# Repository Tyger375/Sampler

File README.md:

# Sampler

**Abstract**\
The project consists of engineering an electronic musical sampler from scratch. The work combines hardware development with the implementation of dedicated software, creating a machine equipped with pressure-sensitive pads for managing audio samples, inspired by the history of hip-hop music. This experience, balancing hobby and education, has provided solid technical skills and is conceived to be constantly updated and perfected.

Read the paper [here](https://github.com/Tyger375/Sampler/blob/main/docs/out/out.pdf) \
*made with [btex](https://github.com/Tyger375/btex)*

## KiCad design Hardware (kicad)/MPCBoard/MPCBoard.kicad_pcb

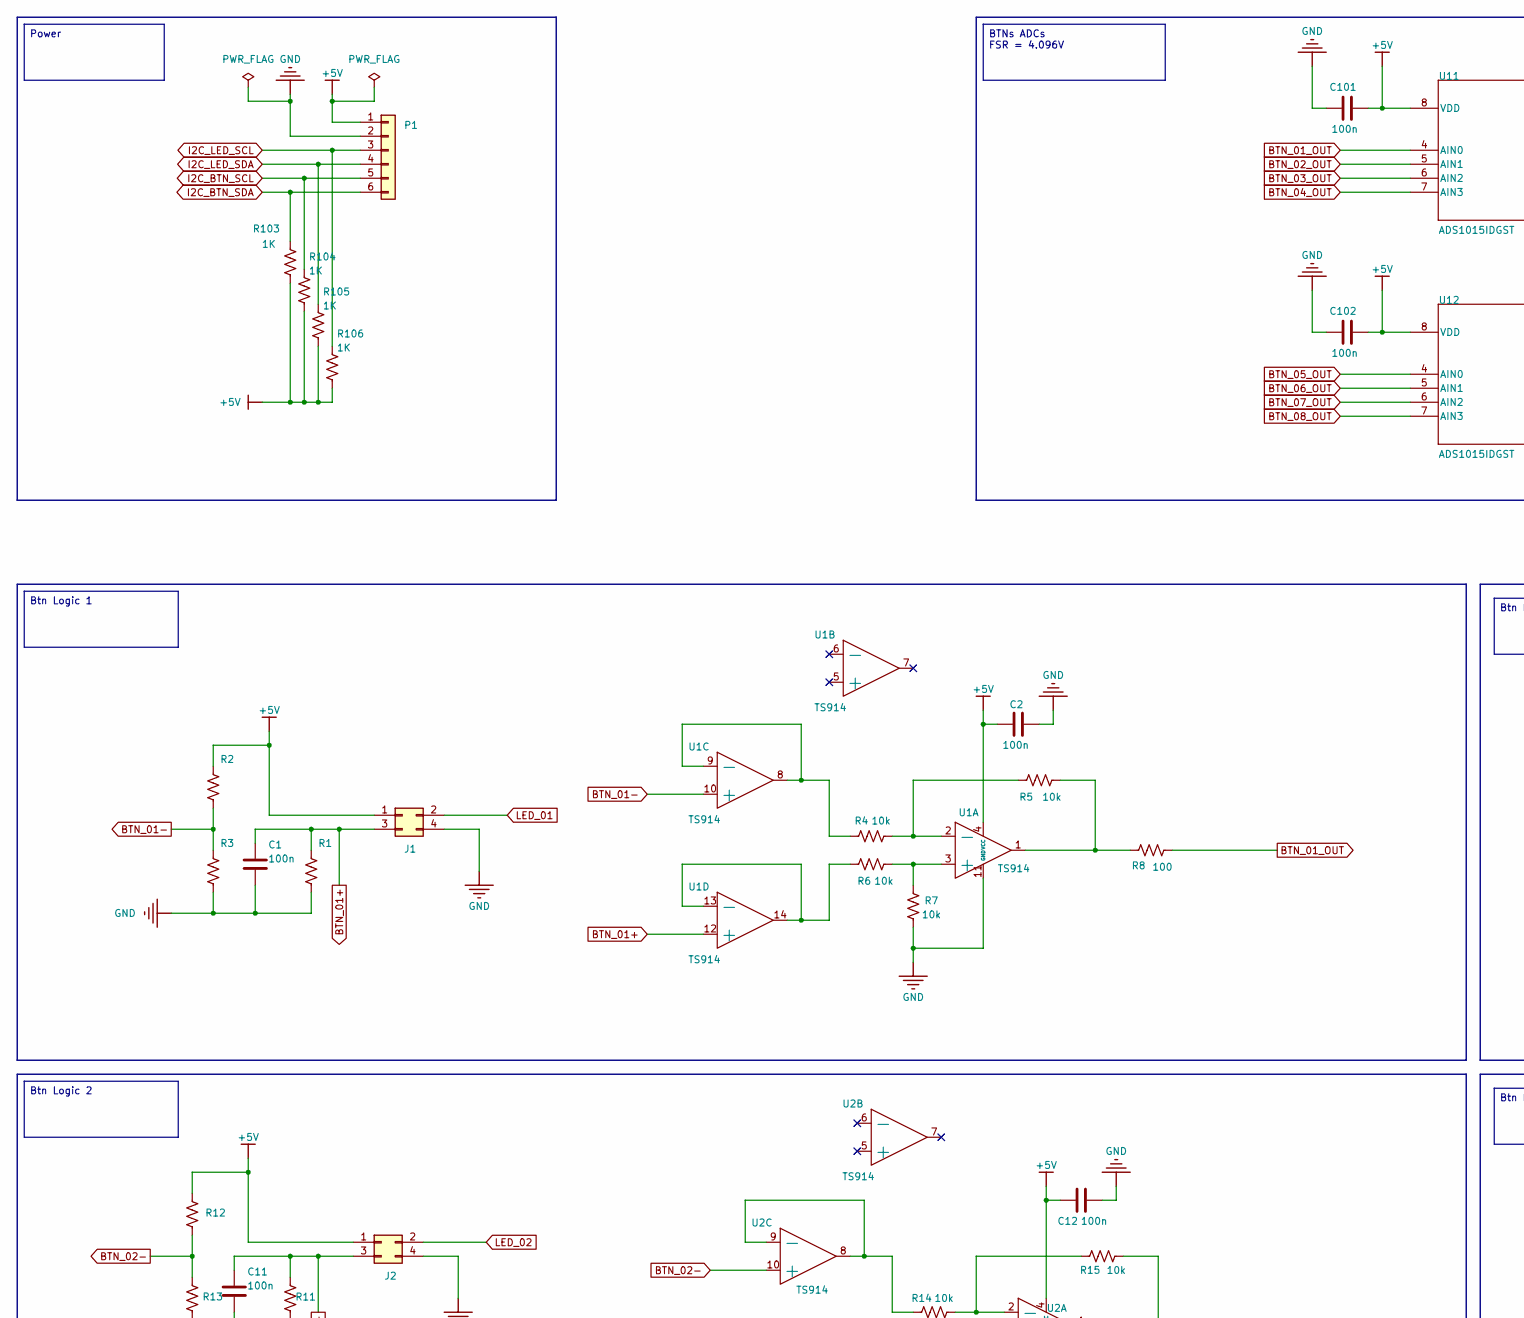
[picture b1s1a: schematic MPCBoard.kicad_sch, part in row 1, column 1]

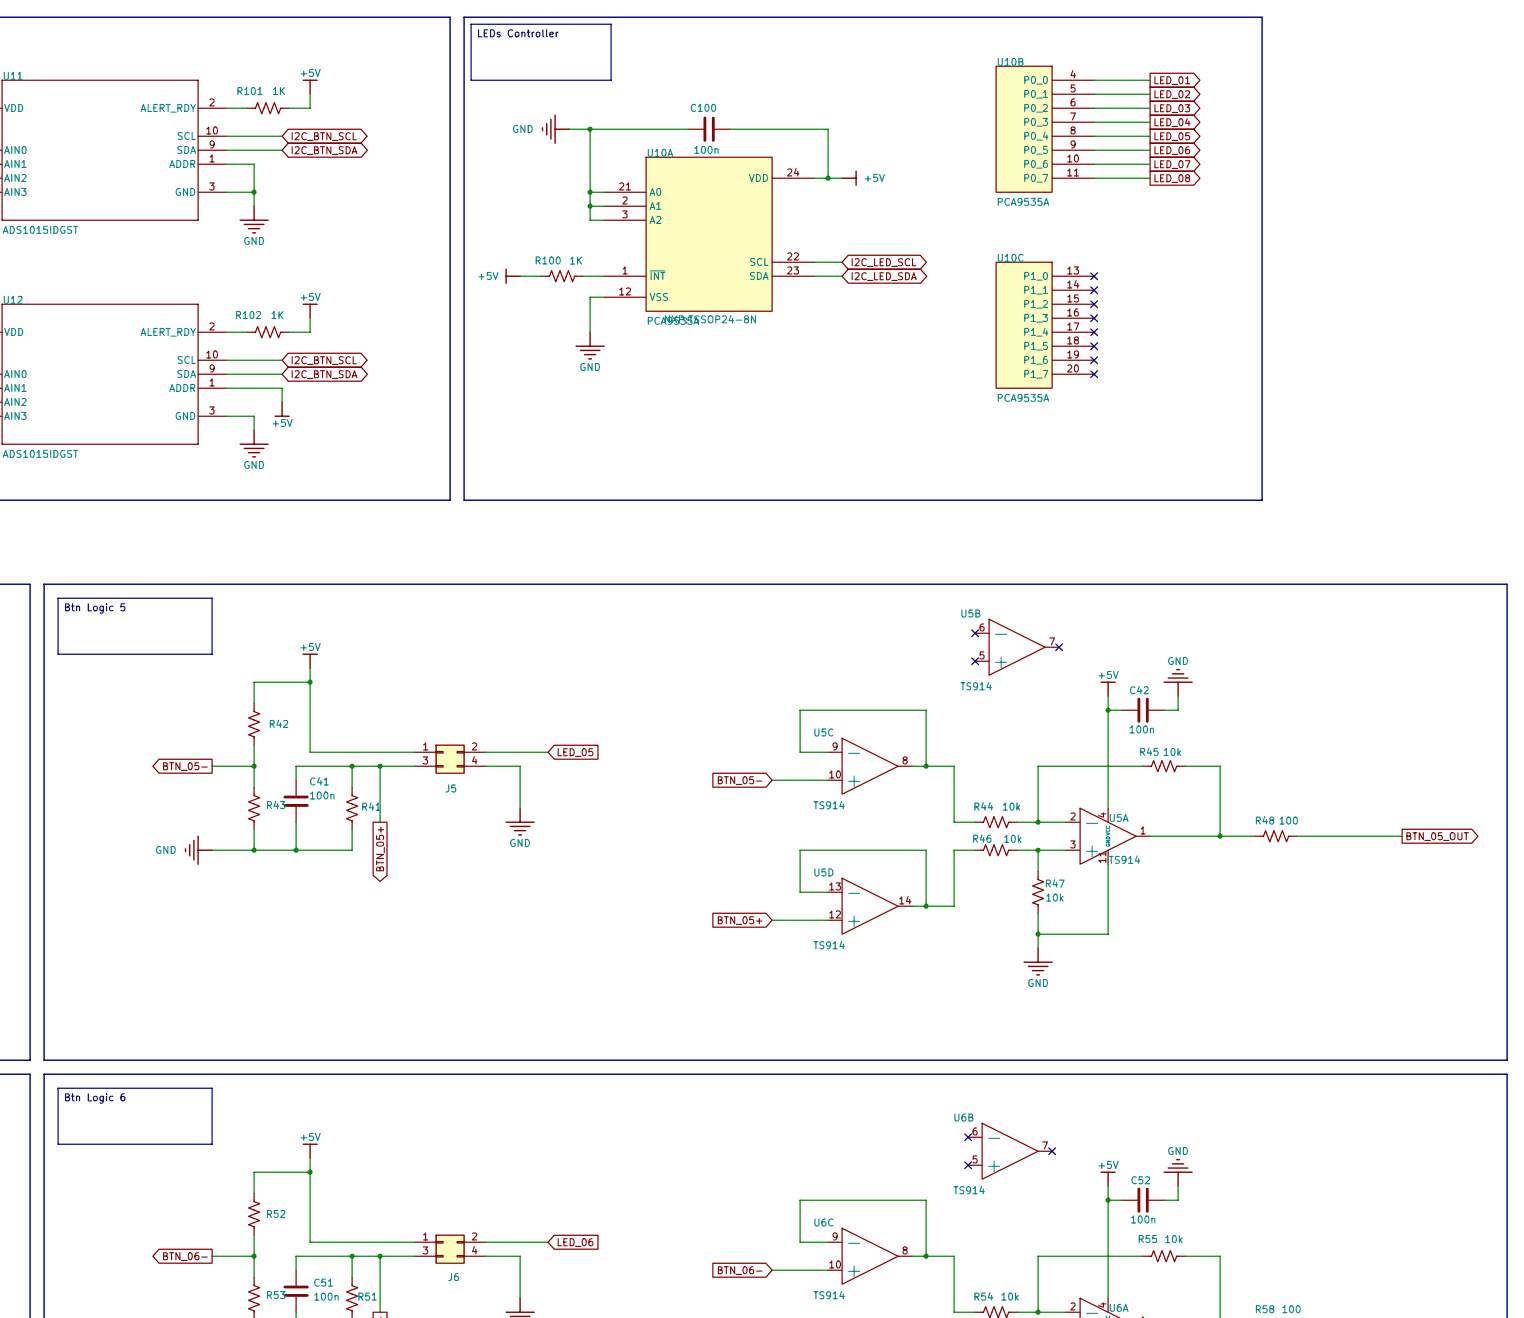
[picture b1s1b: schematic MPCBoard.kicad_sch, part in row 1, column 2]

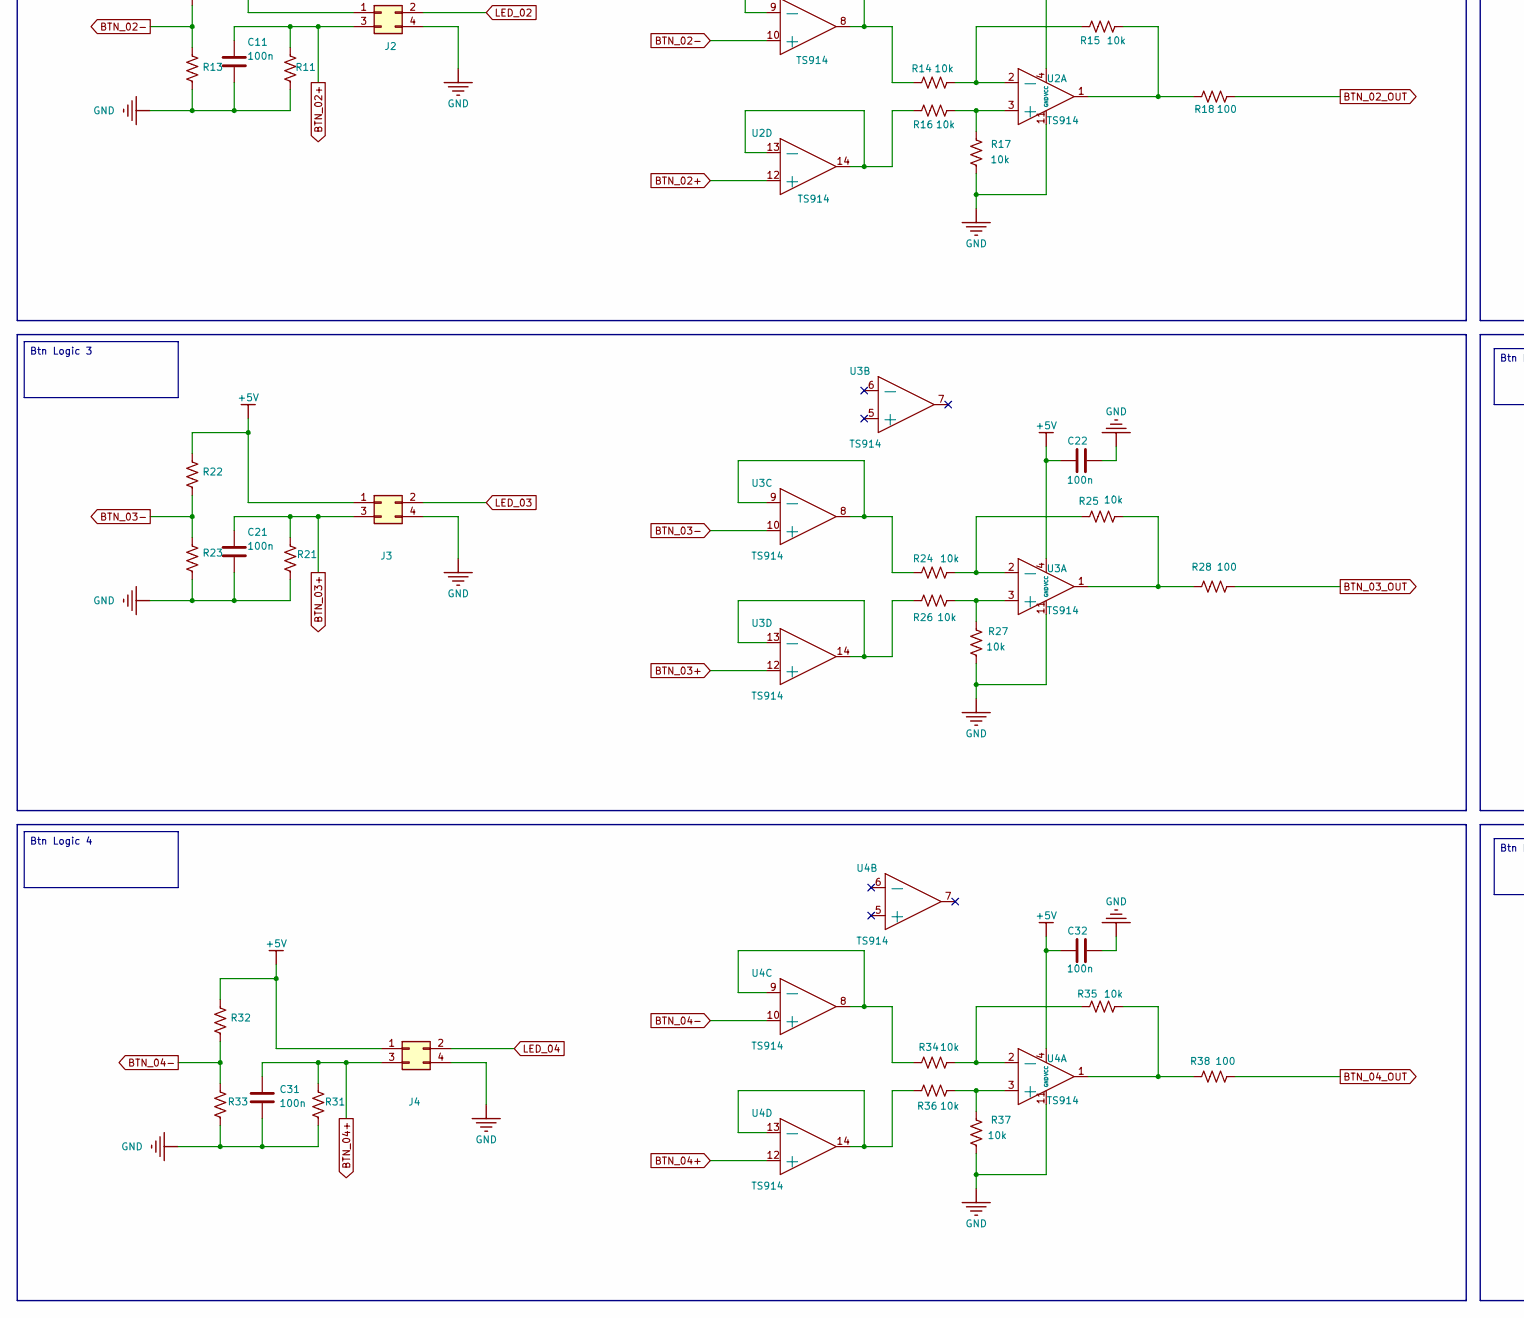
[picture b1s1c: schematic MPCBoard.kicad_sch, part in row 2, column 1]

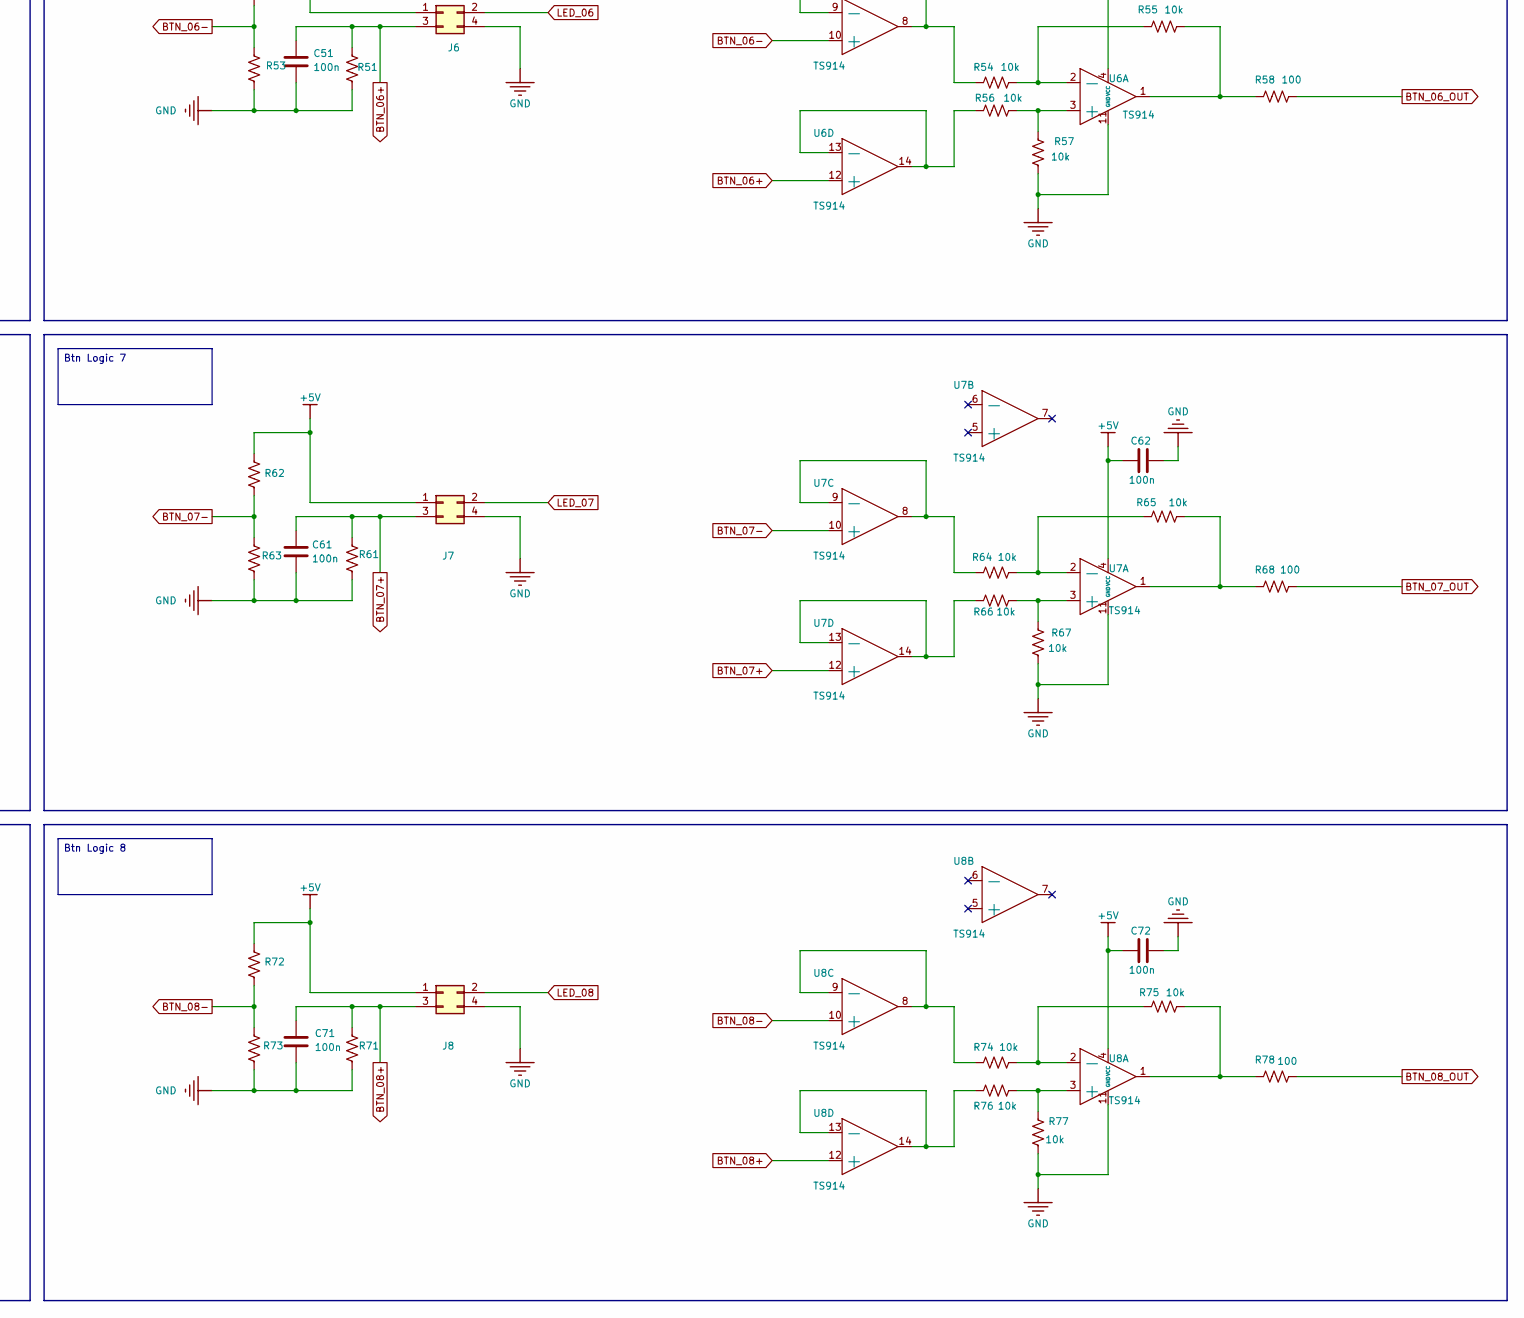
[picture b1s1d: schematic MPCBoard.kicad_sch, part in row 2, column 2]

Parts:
C1, C2, C11, C12, C21, C22, C31, C32, C41, C42, C51, C52, C61, C62, C71, C72, C100, C101, C102: 100n; C_0603_1608Metric_Pad1.08x0.95mm_HandSolder
J1, J2, J3, J4, J5, J6, J7, J8: 62000421821; WORKING VOLTAGE 250V; WITHSTANDING VOLTAGE 500V; MANUFACTURER PART NUMBER 62000421821
P1: 61300611121; WORKING VOLTAGE 250V; WITHSTANDING VOLTAGE 500V; MANUFACTURER PART NUMBER 61300611121
R1, R2, R3, R11, R12, R13, R21, R22, R23, R31, R32, R33, R41, R42, R43, R51, R52, R53, R61, R62, R63, R71, R72, R73: RES; R_0603_1608Metric_Pad0.98x0.95mm_HandSolder
R4, R5, R6, R7, R14, R15, R16, R17, R24, R25, R26, R27, R34, R35, R36, R37, R44, R45, R46, R47, R54, R55, R56, R57, R64, R65, R66, R67, R74, R75, R76, R77: 10k; R_0603_1608Metric_Pad0.98x0.95mm_HandSolder
R8, R18, R28, R38, R48, R58, R68, R78: 100; R_0603_1608Metric_Pad0.98x0.95mm_HandSolder
R100, R101, R102, R103, R104, R105, R106: 1K; R_0603_1608Metric_Pad0.98x0.95mm_HandSolder
U1, U2, U3, U4, U5, U6, U7, U8: TS914; TS914IDT
U10: PCA9535A; TSSOP24-8N
U11, U12: ADS1015IDGST; SOP50P490X110-10N; MANUFACTURER_PART_NUMBER ADS1015IDGST

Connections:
+5V: C2.1, C12.1, C22.1, C32.1, C42.1, C52.1, C62.1, C72.1, C100.2, C101.2, C102.2, J1.1, J2.1, J3.1, J4.1, J5.1, J6.1, J7.1, J8.1, P1.1, R2.1, R12.1, R22.1, R32.1, R42.1, R52.1, R62.1, R72.1, R100.1, R101.2, R102.2, R103.2, R104.2, R105.2, R106.2, U1.4 (VCC), U2.4 (VCC), U3.4 (VCC), U4.4 (VCC), U5.4 (VCC), U6.4 (VCC), U7.4 (VCC), U8.4 (VCC), U10.24 (VDD), U11.8 (VDD), U12.1 (ADDR), U12.8 (VDD)
BTN_01+: C1.1, J1.3, R1.1, U1.12 (+)
BTN_01-: R2.2, R3.1, U1.10 (+)
BTN_01_OUT: R8.2, U11.4 (AIN0)
BTN_02+: C11.1, J2.3, R11.1, U2.12 (+)
BTN_02-: R12.2, R13.1, U2.10 (+)
BTN_02_OUT: R18.2, U11.5 (AIN1)
BTN_03+: C21.1, J3.3, R21.1, U3.12 (+)
BTN_03-: R22.2, R23.1, U3.10 (+)
BTN_03_OUT: R28.2, U11.6 (AIN2)
BTN_04+: C31.1, J4.3, R31.1, U4.12 (+)
BTN_04-: R32.2, R33.1, U4.10 (+)
BTN_04_OUT: R38.2, U11.7 (AIN3)
BTN_05+: C41.1, J5.3, R41.1, U5.12 (+)
BTN_05-: R42.2, R43.1, U5.10 (+)
BTN_05_OUT: R48.2, U12.4 (AIN0)
BTN_06+: C51.1, J6.3, R51.1, U6.12 (+)
BTN_06-: R52.2, R53.1, U6.10 (+)
BTN_06_OUT: R58.2, U12.5 (AIN1)
BTN_07+: C61.1, J7.3, R61.1, U7.12 (+)
BTN_07-: R62.2, R63.1, U7.10 (+)
BTN_07_OUT: R68.2, U12.6 (AIN2)
BTN_08+: C71.1, J8.3, R71.1, U8.12 (+)
BTN_08-: R72.2, R73.1, U8.10 (+)
BTN_08_OUT: R78.2, U12.7 (AIN3)
GND: C1.2, C2.2, C11.2, C12.2, C21.2, C22.2, C31.2, C32.2, C41.2, C42.2, C51.2, C52.2, C61.2, C62.2, C71.2, C72.2, C100.1, C101.1, C102.1, J1.4, J2.4, J3.4, J4.4, J5.4, J6.4, J7.4, J8.4, P1.2, R1.2, R3.2, R7.2, R11.2, R13.2, R17.2, R21.2, R23.2, R27.2, R31.2, R33.2, R37.2, R41.2, R43.2, R47.2, R51.2, R53.2, R57.2, R61.2, R63.2, R67.2, R71.2, R73.2, R77.2, U1.11 (GND), U2.11 (GND), U3.11 (GND), U4.11 (GND), U5.11 (GND), U6.11 (GND), U7.11 (GND), U8.11 (GND), U10.2 (A1), U10.3 (A2), U10.12 (VSS), U10.21 (A0), U11.1 (ADDR), U11.3 (GND), U12.3 (GND)
I2C_BTN_SCL: P1.5, R104.1, U11.10 (SCL), U12.10 (SCL)
I2C_BTN_SDA: P1.6, R103.1, U11.9 (SDA), U12.9 (SDA)
I2C_LED_SCL: P1.3, R106.1, U10.22 (SCL)
I2C_LED_SDA: P1.4, R105.1, U10.23 (SDA)
LED_01: J1.2, U10.4 (P0_0)
LED_02: J2.2, U10.5 (P0_1)
LED_03: J3.2, U10.6 (P0_2)
LED_04: J4.2, U10.7 (P0_3)
LED_05: J5.2, U10.8 (P0_4)
LED_06: J6.2, U10.9 (P0_5)
LED_07: J7.2, U10.10 (P0_6)
LED_08: J8.2, U10.11 (P0_7)
unnamed: R5.2, R8.1, U1.1
unnamed: R15.2, R18.1, U2.1
unnamed: R25.2, R28.1, U3.1
unnamed: R35.2, R38.1, U4.1
unnamed: R45.2, R48.1, U5.1
unnamed: R55.2, R58.1, U6.1
unnamed: R65.2, R68.1, U7.1
unnamed: R75.2, R78.1, U8.1
unnamed: R6.2, R7.1, U1.3 (+)
unnamed: R4.2, R5.1, U1.2 (-)
unnamed: R4.1, U1.8, U1.9 (-)
unnamed: R6.1, U1.13 (-), U1.14
unnamed: R16.2, R17.1, U2.3 (+)
unnamed: R14.2, R15.1, U2.2 (-)
unnamed: R14.1, U2.8, U2.9 (-)
unnamed: R16.1, U2.13 (-), U2.14
unnamed: R26.2, R27.1, U3.3 (+)
unnamed: R24.2, R25.1, U3.2 (-)
unnamed: R24.1, U3.8, U3.9 (-)
unnamed: R26.1, U3.13 (-), U3.14
unnamed: R36.2, R37.1, U4.3 (+)
unnamed: R34.2, R35.1, U4.2 (-)
unnamed: R34.1, U4.8, U4.9 (-)
unnamed: R36.1, U4.13 (-), U4.14
unnamed: R46.2, R47.1, U5.3 (+)
unnamed: R44.2, R45.1, U5.2 (-)
unnamed: R44.1, U5.8, U5.9 (-)
unnamed: R46.1, U5.13 (-), U5.14
unnamed: R56.2, R57.1, U6.3 (+)
unnamed: R54.2, R55.1, U6.2 (-)
unnamed: R54.1, U6.8, U6.9 (-)
unnamed: R56.1, U6.13 (-), U6.14
unnamed: R66.2, R67.1, U7.3 (+)
unnamed: R64.2, R65.1, U7.2 (-)
unnamed: R64.1, U7.8, U7.9 (-)
unnamed: R66.1, U7.13 (-), U7.14
unnamed: R76.2, R77.1, U8.3 (+)
unnamed: R74.2, R75.1, U8.2 (-)
unnamed: R74.1, U8.8, U8.9 (-)
unnamed: R76.1, U8.13 (-), U8.14
unnamed: R100.2, U10.1 (~INT)
unnamed: R101.1, U11.2 (ALERT_RDY)
unnamed: R102.1, U12.2 (ALERT_RDY)

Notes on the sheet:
Btn Logic 3
BTNs ADCs FSR = 4.096V
Btn Logic 1
Power
Btn Logic 6
Btn Logic 7
Btn Logic 5
Btn Logic 4
Btn Logic 8
Btn Logic 2
LEDs Controller

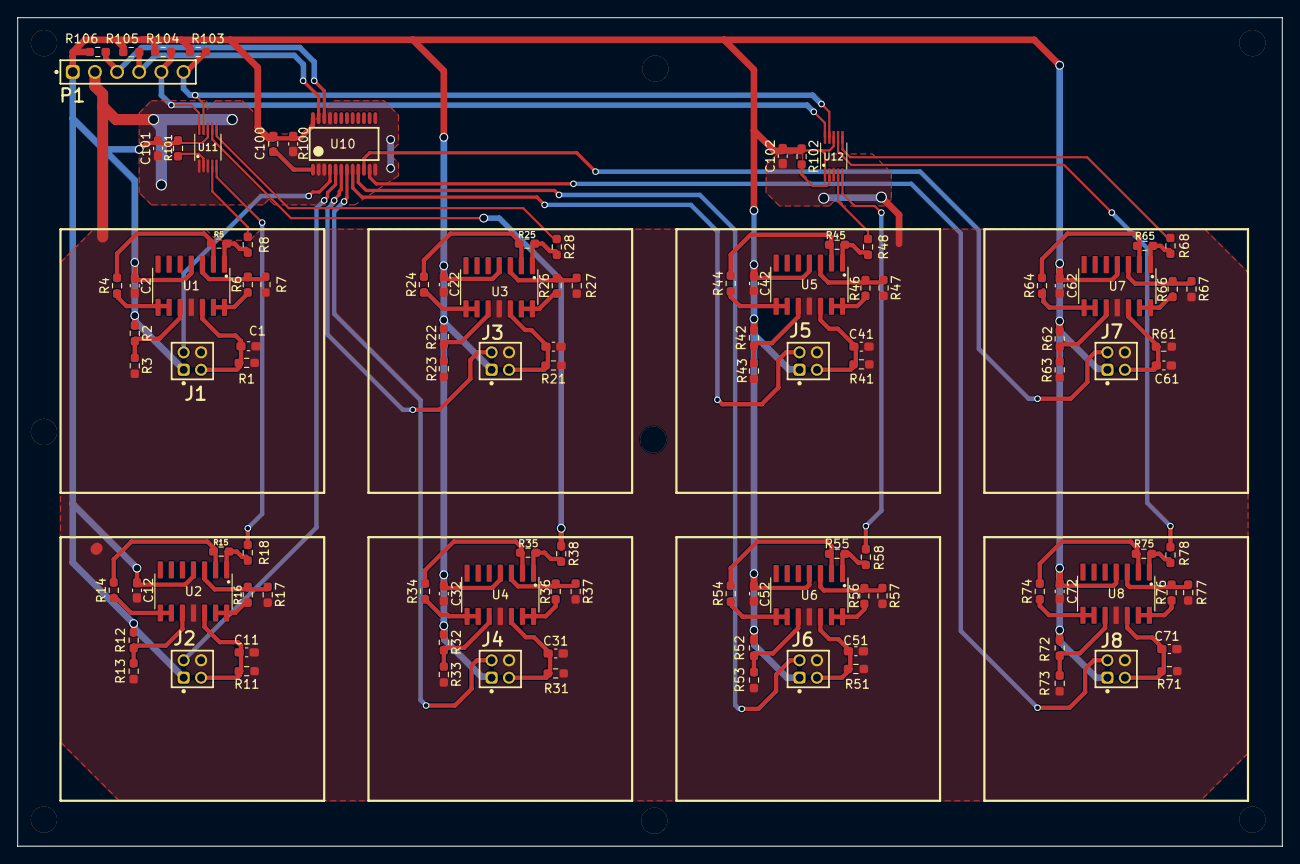
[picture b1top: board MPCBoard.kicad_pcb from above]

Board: 2 copper layers, 145.0 x 95.0 mm, 110 parts (0 on the bottom side), 81 nets.

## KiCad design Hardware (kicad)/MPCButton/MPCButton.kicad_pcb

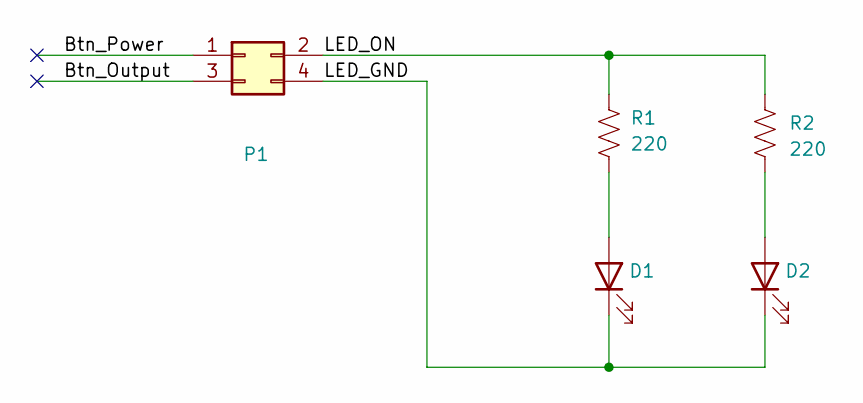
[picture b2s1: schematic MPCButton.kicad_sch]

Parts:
D1, D2: Red, 2V, 120°; WL-SMCW_0603_150060xx75000; FORWARD VOLTAGE 2V; MANUFACTURER PART NUMBER 150060RS73220
P1: 62100421921; WORKING VOLTAGE 200V; WITHSTANDING VOLTAGE 500V; MANUFACTURER PART NUMBER 62100421921
R1, R2: 220; R_0603_1608Metric_Pad0.98x0.95mm_HandSolder

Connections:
/Btn_Output: P1.3
/Btn_Power: P1.1
/LED_GND: D1.1 (K), D2.1 (K), P1.4
/LED_ON: P1.2, R1.1, R2.1
unnamed: D1.2 (A), R1.2
unnamed: D2.2 (A), R2.2

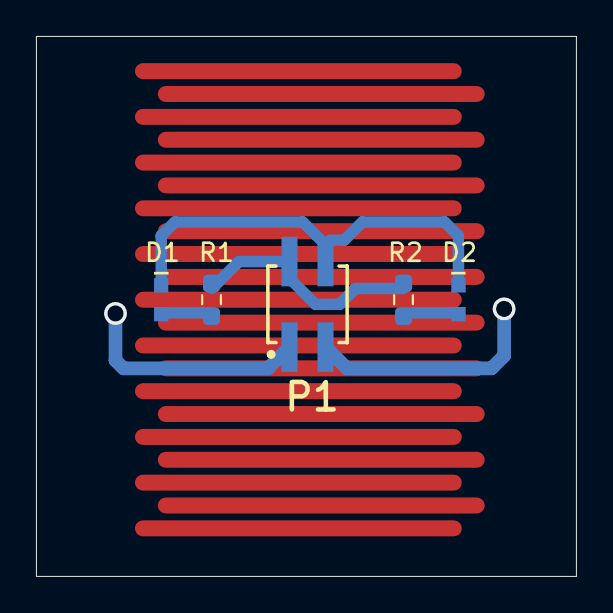
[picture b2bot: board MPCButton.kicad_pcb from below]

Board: 2 copper layers, 30.0 x 30.0 mm, 5 parts (5 on the bottom side), 4 nets.

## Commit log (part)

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2026-02-19 added readme files
2026-02-19 full restructuring of graphics library
2026-02-22 refactor graphics library
2026-03-07 pads_component
2026-03-08 vendor support (read and write configurations)
2026-03-08 fix vendor_respond and sequencer pad numbers
2026-03-26 migrating to esp32-rust
2026-03-27 migrating ads1015
2026-03-28 migrating to rust
2026-04-01 rust settings_manager and screens
2026-04-02 adding vendor communication
2026-04-02 adding pad_settings screen
2026-04-05 adding sequencer and shortcuts
2026-04-07 sequencer screen
2026-04-24 sequencer features and bug fixes
2026-04-24 remove test program
2026-04-24 documentation
2026-04-24 removed 3d models
2026-05-02 fix kicad projects
2026-05-04 docs
2026-05-09 gitignore
2026-05-14 bug fix

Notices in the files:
parts and their libraries:
COPYRIGHT: Copyright (C) 2025 Ultra Librarian. All rights reserved.
